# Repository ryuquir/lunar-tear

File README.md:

# Lunar Tear

Private server research project for a certain discontinued mobile game.
Discord server: https://discord.gg/G3anrfcV

## How To Launch The Server

### Prerequisites

- Go 1.24+
- Populated `server/assets/` directory

### Regenerate protobuf stubs

```bash
cd server
make proto
```

### Run

```bash
cd server
sudo go run ./cmd/lunar-tear \
  --host 10.0.2.2 \
  --http-port 8080 \
  --scene 13
```

`sudo` is needed because gRPC binds to port 443 (privileged). On Linux you can use `setcap` instead:

```bash
go build -o lunar-tear ./cmd/lunar-tear
sudo setcap cap_net_bind_service=+ep ./lunar-tear
./lunar-tear --host 10.0.2.2 --http-port 8080 --scene 13
```

### Ports

| Protocol | Port | Notes                                                |
| -------- | ---- | ---------------------------------------------------- |
| gRPC     | 443  | hardcoded by the client, not configurable            |
| HTTP     | 8080 | Octo asset API + game web pages (`--http-port` flag) |

### Flags

| Flag                   | Default             | Description                                              |
| ---------------------- | ------------------- | -------------------------------------------------------- |
| `--host`               | `127.0.0.1`         | hostname/IP given to the client                          |
| `--http-port`          | `8080`              | HTTP/Octo server port                                    |
| `--resources-base-url` | (derived from host) | base URL for list.bin rewrite (must be exactly 43 chars) |
| `--scene`              | `0`                 | bootstrap new users to scene N (0 = fresh start)         |

### `--resources-base-url`

Overrides the base URL the client uses to fetch resources. The replacement string **must be exactly 43 characters**. If omitted, the server derives it from `--host` and `--http-port` automatically (when the result happens to be 43 characters). If the length doesn't match, the server logs a warning and serves the resource list unchanged.

```bash
sudo go run ./cmd/lunar-tear \
  --host 10.0.2.2 \
  --http-port 8080 \
  --resources-base-url "http://192.168.1.50:8080/res-bundle-srv" \
  --scene 13
```

> **Tip:** verify the length with `printf "your-url-here" | wc -c`.

## ⚠️ Legal Disclaimer

**Lunar Tear** is a fan-made, non-commercial **preservation and research project** dedicated to keeping a certain discontinued mobile game playable for educational and archival purposes.

- This project is **not affiliated with**, **endorsed by**, or **approved by** the original publisher or any of its subsidiaries.
- All trademarks, copyrights, and intellectual property related to the original game and its associated franchises belong to their respective owners.
- All code in this repository is original work developed through clean-room reverse engineering for interoperability with the game client.
- No copyrighted game assets, binaries, or master data are distributed in this repository.

**Use at your own risk.** The author assumes no liability for any damages or legal consequences that may arise from using this software. By using or contributing to this project, you are solely responsible for ensuring your usage complies with all applicable laws in your jurisdiction.

This project is released under the [MIT License](LICENSE).

**If you are a rights holder with concerns regarding this project**, please contact me directly.

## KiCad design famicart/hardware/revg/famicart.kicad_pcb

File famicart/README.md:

# famicart — RP2040/RP2350 ファミコン・マルチマッパー・カートリッジ ファームウェア＋基板

ファミコン（NES）の公式・ライセンス品 2,233 タイトルで使われた 92 種のマッパーを調査し、その全種（タイトル数ベース **99.0%**（2,211 本）。残り 22 本はデータベース上の不良ダンプ）に加え、基板名の記録がない市販 FC ソフト用のマッパーも含めて計 98 種をソフトウェアで再現する 1 チップ・カートリッジのファームウェアです。フラッシュに書き込んだ ROM 画像からマッパーを自動判別し、プロファイル指定で「MMC5 のバンク機能 + VRC7 音源」のような拡張 IC の組み合わせも可能にします。

> **重要な前提**: Seeed Studio XIAO RP2040 は GPIO が 11 本しかなく、単体ではカートリッジバス（最低 26 本）を駆動できません。理由と数値は [docs/01_feasibility.md](docs/01_feasibility.md) を参照。そのため **rev C 基板では基板直付けの RP2350B（GPIO 48 本）がバスを担当し、XIAO RP2040 は拡張音源コプロセッサ**として同居します（[docs/04_hardware.md](docs/04_hardware.md) の rev C 節）。rev A/B は Pico / Pico 2 モジュール 1 個の構成です。

## 状態（フェーズ 1・2 完了、フェーズ 3 = 実機検証 待ち）

| 項目 | 状態 |
|---|---|
| マッパー調査・集計（Mesen DB 由来） | 完了 → [docs/03_mapper_coverage.md](docs/03_mapper_coverage.md) |
| コア（バンク表・マッパー 99 種〔ライセンス品の 98 種＋自作向けのマッパー 30（UNROM 512、フラッシュ自己書き込み対応）〕・ROM 判別・DB 2,840 件・プロファイル） | 実装済み、ホストテスト 2,122 チェック通過 |
| 拡張音源レジスタ・ルーター（組み合わせ機構） | 実装済み |
| 拡張音源の合成（VRC6/VRC7/MMC5/N163/5B/FDS、`src/core/audio/synth.c`） | 実装済み（6 音源とも発音をホストテストで確認、VRC7 は OPLL 近似）。rev C では XIAO 側で動作 |
| PIO バス・フロントエンド、2 コア処理、PWM 音声出力 | 実装済み・**実機未検証** |
| USB-CDC コマンド（INFO / RESET / BOOTSEL / LOAD / PROFILE）と転送ツール `tools/fcload.py` | 実装済み・**実機未検証** |
| Pico / Pico 2 / RP2350B / XIAO（コプロセッサ）向けビルド | 通過（Pico: text 120KB, BSS 249KB / RP2350B: text 106KB, BSS 512KB / XIAO audio: text 42KB） |
| 2 MCU 間 UART リンク（3 Mbaud、音源レジスタのストリーム） | 実装済み・**実機未検証** |
| 回路図・基板 rev B（Pico 2、KiCad 7、90×46.1 mm〔※外形は旧寸法で切り欠きなし＝基板単体用。[04](docs/04_hardware.md) の訂正を参照〕、USB-C・リセット付き、未接続 0・DRC 0）・ガーバー・JLCPCB 実装パッケージ | [hardware/](hardware/)、[hardware/jlcpcb/](hardware/jlcpcb/) |
| 回路図・基板 rev C（RP2350B + XIAO RP2040、USB 3 口、リセット端子 J2、未接続 0・DRC 0）・ガーバー・JLCPCB 実装パッケージ | [hardware/revc/](hardware/revc/) |
| 回路図・基板 rev D（**実機動作の本命**: 実カセット型分離構成、RP2350B×2 マッパーチップ + PRG/CHR パラレル NOR 64 MB×2 + F-RAM 128 KB + CHR SRAM 512 KB、**6 層、未接続 0・DRC エラー 0**、起動バンク付き）・ガーバー・JLCPCB 実装パッケージ | [hardware/revd/](hardware/revd/)、[hardware/revd/jlcpcb/](hardware/revd/jlcpcb/)、docs/04_hardware.md の rev D 節 |
| 回路図・基板 rev E（※外形は旧寸法で切り欠きなし＝基板単体用。標準シェルには Pico 2 が 1 枚しか入らないため rev E は標準シェル不可、[04 の訂正](docs/04_hardware.md)）（**実際に作れる安価な版**: Pico 2 ×2 + XIAO RP2350、JLCPCB Basic 部品のみ 10 種・45 点、2 層、未接続 0・DRC エラー 0、MMC5 完全対応の配線）・ガーバー・JLCPCB 実装パッケージ | [hardware/reve/](hardware/reve/)、[docs/06_rev_e_plan.md](docs/06_rev_e_plan.md) |
| 回路図・基板 **rev F2**（rev F の回路を**任天堂の大型シェル**に合わせ、4 資料から作った外形〔切り欠き・スリット・リブ回避。実物では未確認〕で配置、90 × 85.7 mm、Pico 2 ×4 + XIAO、Basic 部品のみ 10 種・54 点、2 層、**未接続 0・DRC エラー 0**） | [hardware/revf2/](hardware/revf2/)、[docs/10_rev_f_board.md](docs/10_rev_f_board.md) |
| 回路図・基板 **rev G**（Pico 2 ×2 ＋ XIAO RP2350 ×2 を基本に、増設 Pico 2 ×2〔512 KB 級の PRG・CHR 用、任意〕、16 MB フラッシュ、microSD〔任意〕。任天堂の大型シェル用 89.6 × 85.7 mm、2 層、Basic 部品のみ 10 種・81 点、**未接続 0・DRC エラー 0**。外形・ビア・シルク・端子部を JLCPCB の製造条件に合わせ、Standard PCBA 用の注文パッケージ（捨て基板を描き込んだデータと、基板だけのデータ）を付けた。検査ツールが 2 つのガーバー ZIP の中身と捨て基板の寸法をデータから測る。設計レビューで見つかった回路の問題〔書き込みストローブ、/ROMSEL、PPU /WE、31 番端子、PPU データ線の直列抵抗など〕を修正。**実機とシェルの実物では未検証、rev G 用のファームは未作成**） | [hardware/revg/](hardware/revg/)（[外形図](hardware/revg/outline.png)、[配置図](hardware/revg/placement.png)、[注文メモ](hardware/revg/jlcpcb/README.md)）、[docs/12_rev_g_plan.md](docs/12_rev_g_plan.md)、ファミコン本体の仕様と全端子は [docs/11_famicom_reference.md](docs/11_famicom_reference.md) |
| 回路図・基板 rev F（rev E + SFC 型コプロセッサ用 Pico 2 ×2、90 × 70.1 mm、Basic 部品のみ 10 種・54 点、2 層、**未接続 0・DRC エラー 0**。外形は旧寸法で切り欠きなし＝基板単体用） | [hardware/revf/](hardware/revf/)、[docs/10_rev_f_board.md](docs/10_rev_f_board.md)、コプロセッサ ABI は [docs/09_coproc_abi.md](docs/09_coproc_abi.md) |
| rev E ファームウェア（U1 CPU バス応答・書き込み取り込み・CHR-RAM 再現・起動手順・ROM ライブラリ、U2 CHR/CIRAM /CE・MMC5 PPU 処理、U3 IRQ・拡張音源、3 台リンク） | 実装済み・3 本ともビルド通過、ホストテスト通過（rev E 分 52 項目、追加マッパー 524 項目）、**実機未検証**。[docs/07_rev_e_firmware.md](docs/07_rev_e_firmware.md) |
| rev D ファームウェア（バンク線出力、2 MCU リンク、外部フラッシュ書き込み、ROM ライブラリ、ブートスタブ） | 実装済み・ビルド通過（U1 text 130 KB / U2 37 KB）、ホストテスト通過、**実機未検証** |

## ビルド

```sh
# ホスト側ユニットテスト
cd famicart/test && make

# ファームウェア（FC_BOARD = pico | pico2 | rp2350b | xiao_audio | xiao_rp2040）
cd famicart && mkdir -p build && cd build
cmake -DPICO_SDK_PATH=/path/to/pico-sdk -DFC_BOARD=pico2 ..
make -j
# -> famicart.uf2 を BOOTSEL モードのドライブへコピー

# rev C 基板は 2 つ書く: 主 MCU（J3 を挿し SW2 を押しながら SW1 を離す）と XIAO（XIAO 自身の USB-C と BOOT ボタン）
cmake -S . -B build-rp2350b   -DFC_BOARD=rp2350b   && cmake --build build-rp2350b   # -> RP2350B へ
cmake -S . -B build-xiao_audio -DFC_BOARD=xiao_audio && cmake --build build-xiao_audio # -> XIAO RP2040 へ
```

## ROM の書き込み（自動判別）

```sh
# そのまま: ヘッダ → CRC32 DB → サイズ推定 の順で自動判別
python3 tools/rom2uf2.py game.nes -o game.uf2 --family rp2350

# マッパーを強制し、VRC7 音源を追加（MMC5 の機能 + VRC7 の音）
python3 tools/rom2uf2.py game.nes -o game.uf2 --mapper 5 --audio vrc7:exclusive --audio mmc5

# レジスタ窓が衝突する組み合わせは窓を移動（VRC6 のレジスタを $C000 へ）
python3 tools/rom2uf2.py game.nes -o game.uf2 --audio vrc6@0xC000
```

## 本体に挿したまま ROM を転送（USB-C）

```sh
pip install pyserial
python3 tools/fcload.py /dev/ttyACM0 info          # 判別結果・バス統計
python3 tools/fcload.py /dev/ttyACM0 load game.nes # 転送 → カートリッジ自動再起動 → 本体のリセットを押す
python3 tools/fcload.py /dev/ttyACM0 reset         # ソフトからカートリッジをリセット
python3 tools/fcload.py /dev/ttyACM0 bootsel       # ファーム更新用 UF2 モードへ
```

ROM はフラッシュ先頭から 256KB の位置（`FC_FLASH_ROM_SLOT`）に、48 バイトのプロファイル（256 バイト境界にパディング）＋画像の形で書き込まれます。ツールを介さず `.nes` を直接その位置に焼いた場合もヘッダ/DB で判別します。起動後、USB CDC（115200）に判別結果とバス統計が 2 秒ごとに出ます。

## データベースの再生成

```sh
python3 tools/gen_romdb.py   # data/MesenNesDB.txt -> src/core/romdb_gen.h, docs/03_mapper_coverage.md
```

## ドキュメント

- [01 実現可能性](docs/01_feasibility.md) — ピン数・タイミング・メモリの数値と結論
- [02 ファームウェア構成](docs/02_architecture.md) — 高速パス、マッパー IF、音源ルーター、判別フロー、既知の制約
- [03 マッパー集計](docs/03_mapper_coverage.md) — 92 種の本数・サブマッパー・代表基板・実装状況
- [04 ハードウェア](docs/04_hardware.md) — KiCad プロジェクト、基板寸法、GPIO 割当、部品表、音声ミックス回路

## 基板の再生成（KiCad 7 + Freerouting）

```sh
cd famicart/tools/pcb
python3 gen_sch.py && python3 route_pcb.py && python3 gen_bom.py && python3 gen_jlc.py            # rev B -> hardware/
FC_DESIGN=design_revc FC_HW_DIR=../../hardware/revc python3 gen_sch.py   # rev C -> hardware/revc/（route_pcb / gen_bom / gen_jlc も同じ環境変数で）
FC_DESIGN=design_revd FC_HW_DIR=../../hardware/revd FC_LAYERS=6 FC_STUBS=1 FC_TRACK=0.1 FC_CLEAR=0.1 FC_VIA=0.5 FC_VIA_DRILL=0.2 python3 route_pcb.py   # rev D（6 層）
python3 finish_route.py ../../hardware/revd/famicart.kicad_pcb   # Freerouting が残した接続を仕上げる（その後 route_pcb.py export）
```

## ロードマップ

1. **フェーズ 3**: 基板の試作・実機検証（ロジアナでタイミング確認）、配線の手直し、VRC7 音色の実機比較による校正、USB マスストレージからの ROM 選択、セーブ（バッテリ RAM）のフラッシュ退避
2. **フェーズ 4（rev D 向けファーム）**: 実装済み（バンク出力・リンク・フラッシュ書き込み・ライブラリ・ブートスタブ）。残り: 起動メニュー（コントローラでライブラリ選択）、MMC5 $5204 状態の U2→U1 同期、$6000 PRG-ROM マッパーの F-RAM コピー対応
3. **フェーズ 5（実機ブリングアップ）**: 基板到着後 `FLASHID` → `BOOTBANK` → `libadd` NROM → MMC1 → MMC3 → MMC5 の順に確認。ロジアナで M2 ↔ バンク線・/RD ↔ CHR バンク線の遅延を測る
4. 未実装マッパー（海賊版マルチカート系）は対象外のまま

## ライセンス・出典

ファームウェアはリポジトリのライセンスに従います。`data/MesenNesDB.txt` は Mesen プロジェクト配布の生成データ（NesCartDB および NewRisingSun の NES 2.0 header database 由来）で、マッパー判別用のメタデータのみを利用しています。ゲーム ROM は含みません。

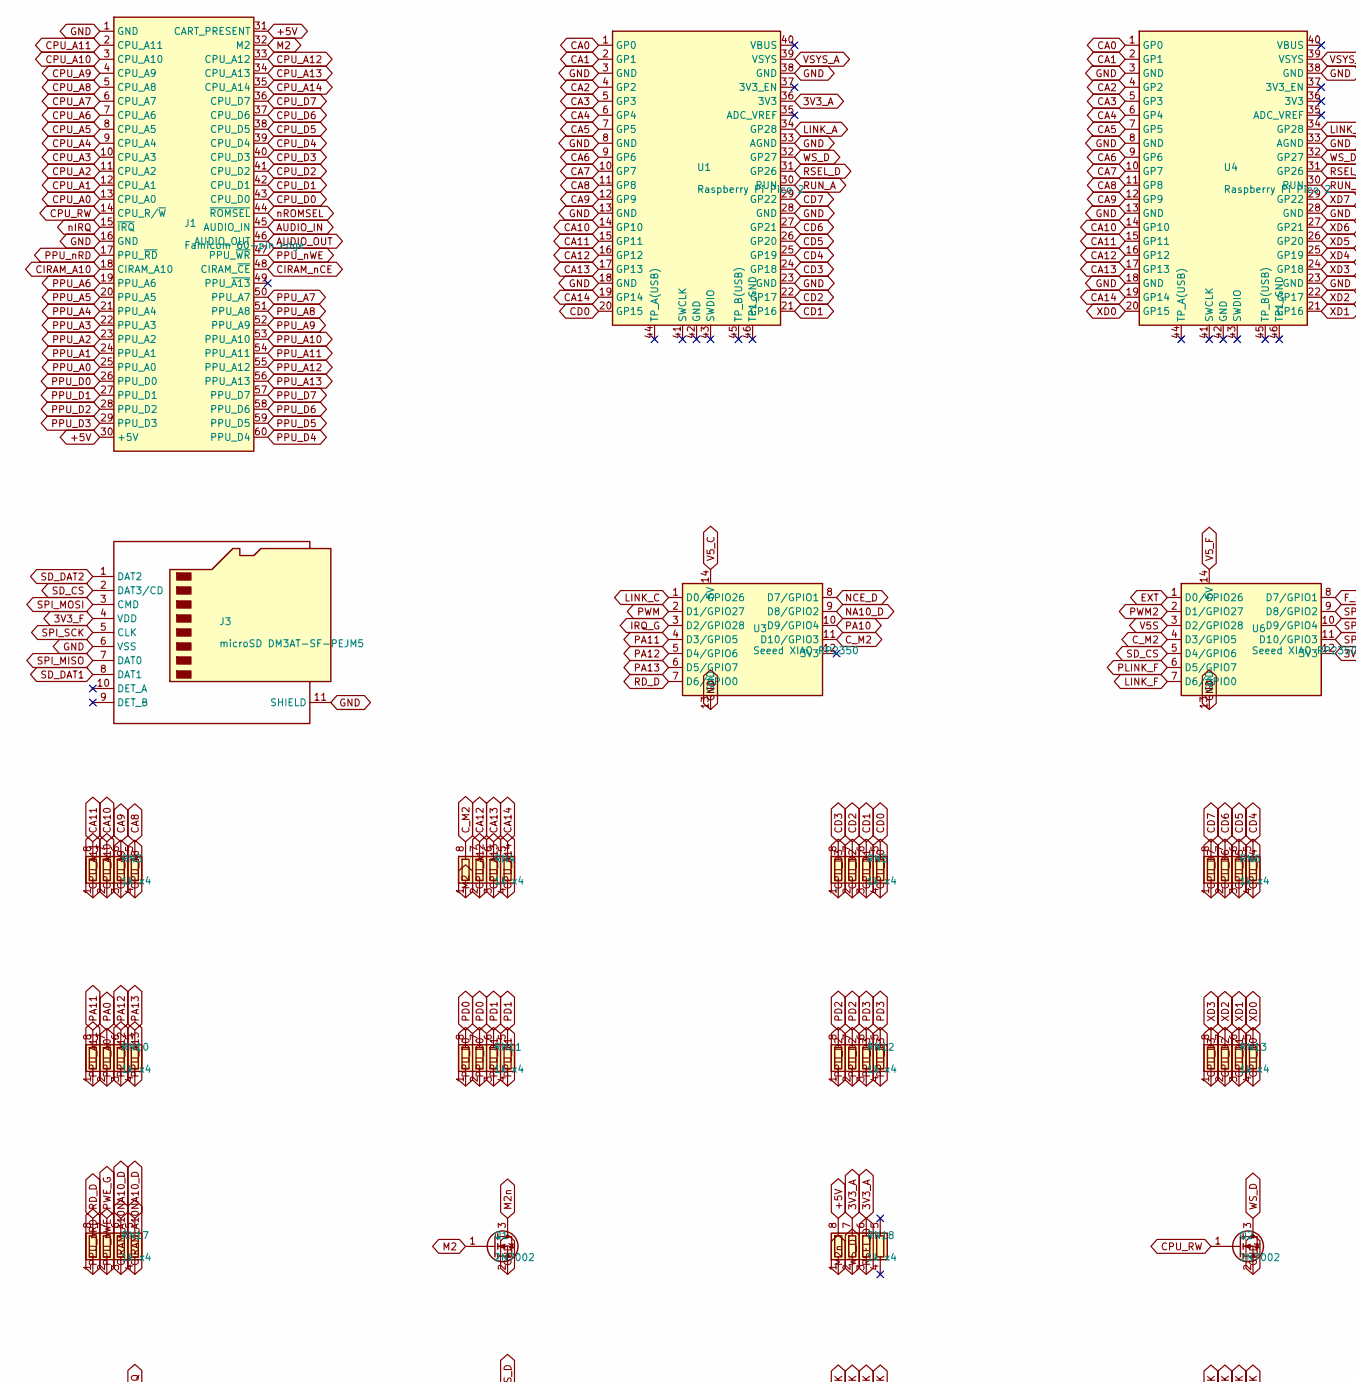
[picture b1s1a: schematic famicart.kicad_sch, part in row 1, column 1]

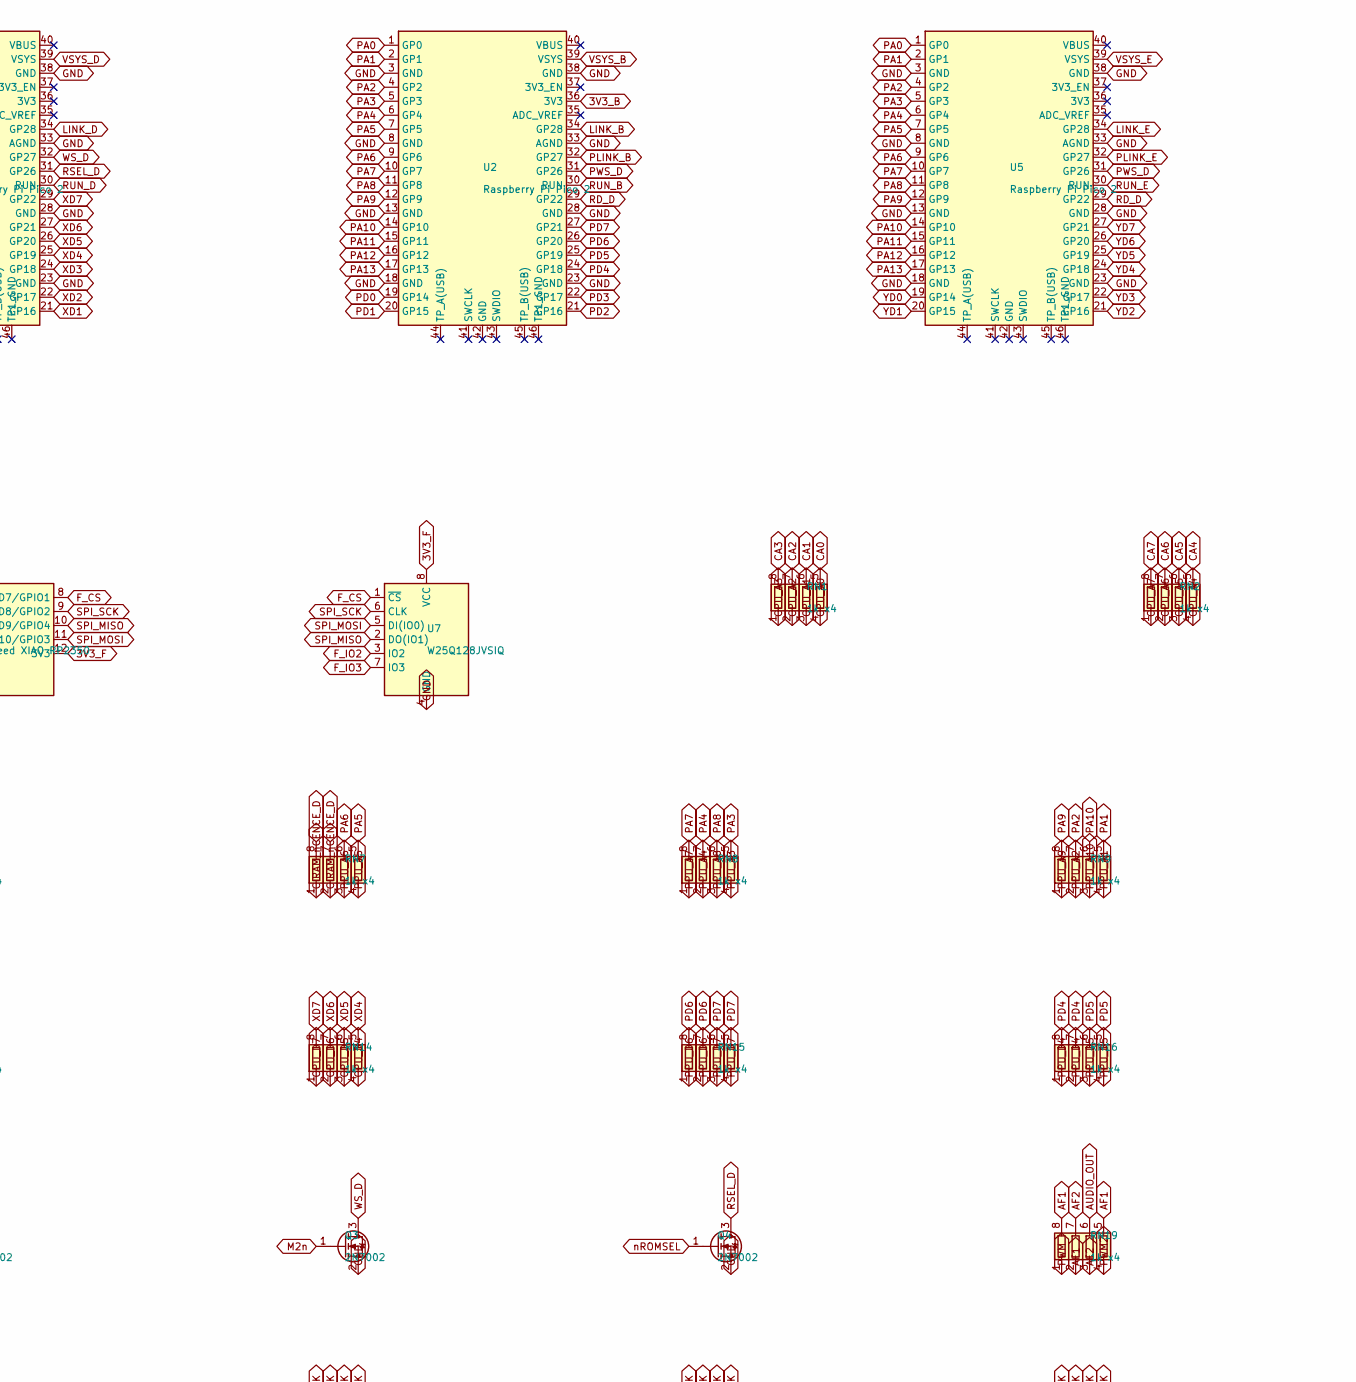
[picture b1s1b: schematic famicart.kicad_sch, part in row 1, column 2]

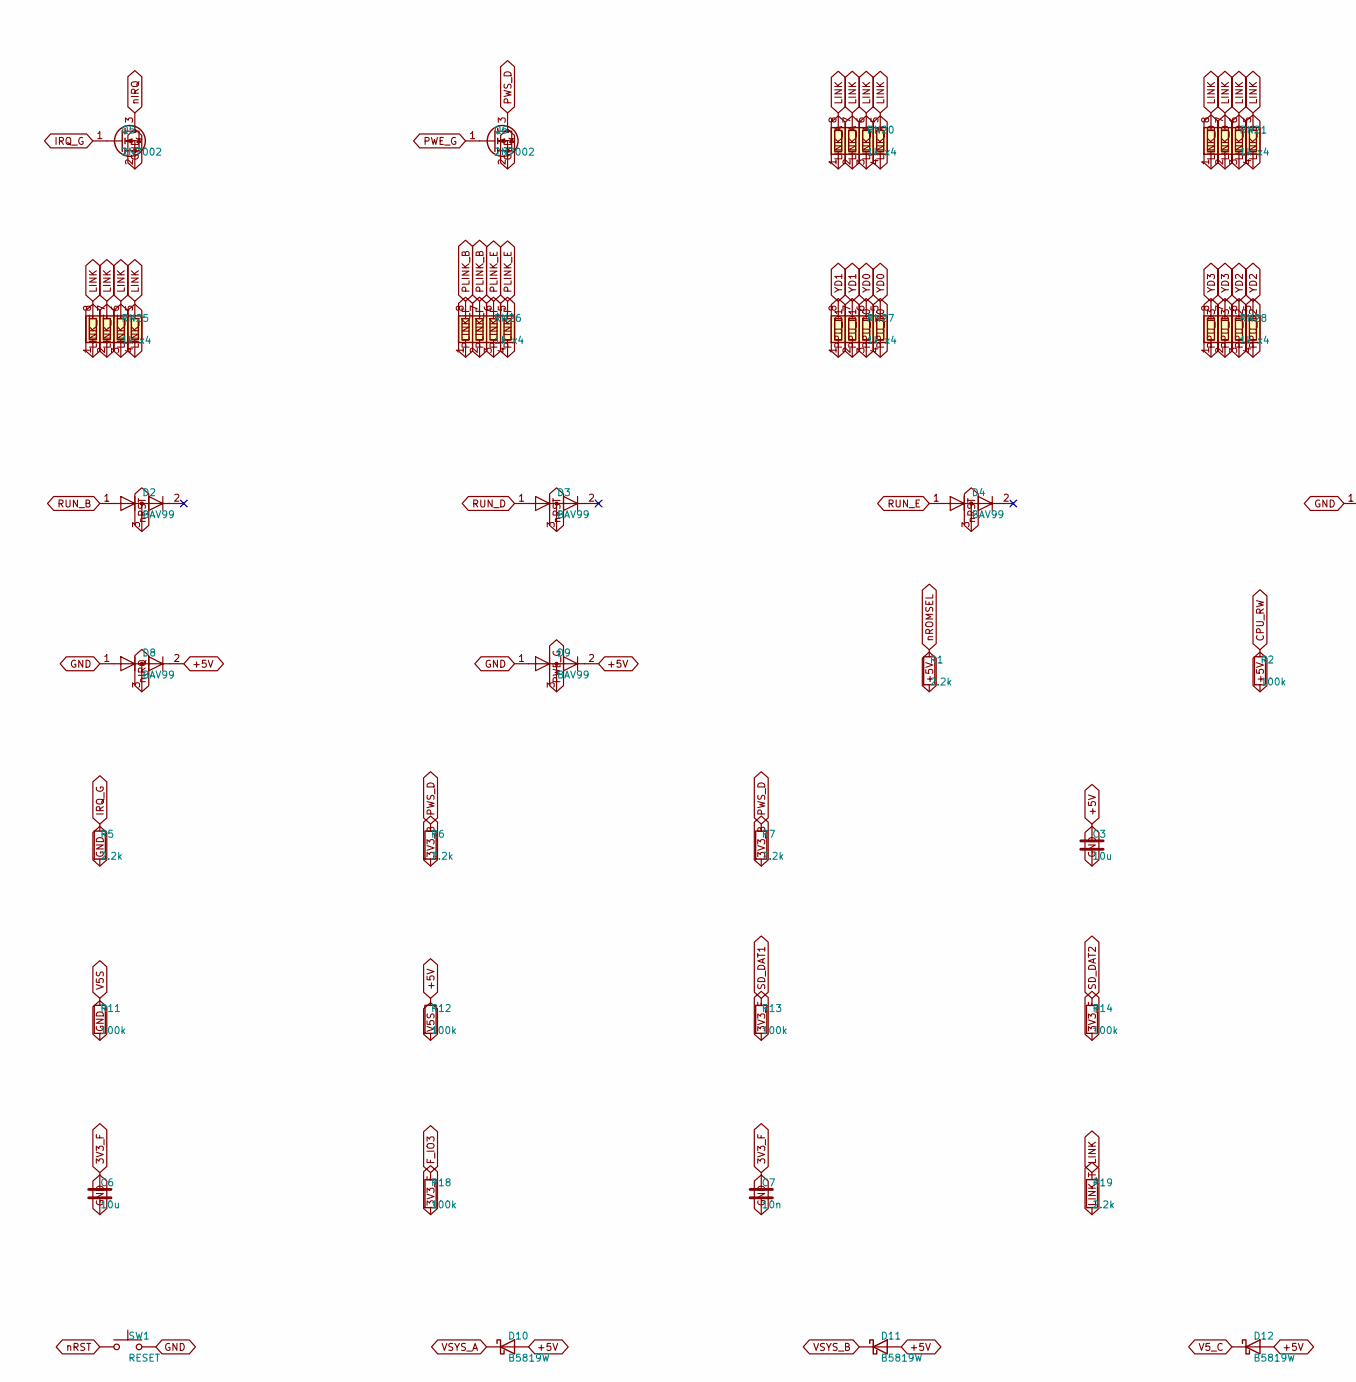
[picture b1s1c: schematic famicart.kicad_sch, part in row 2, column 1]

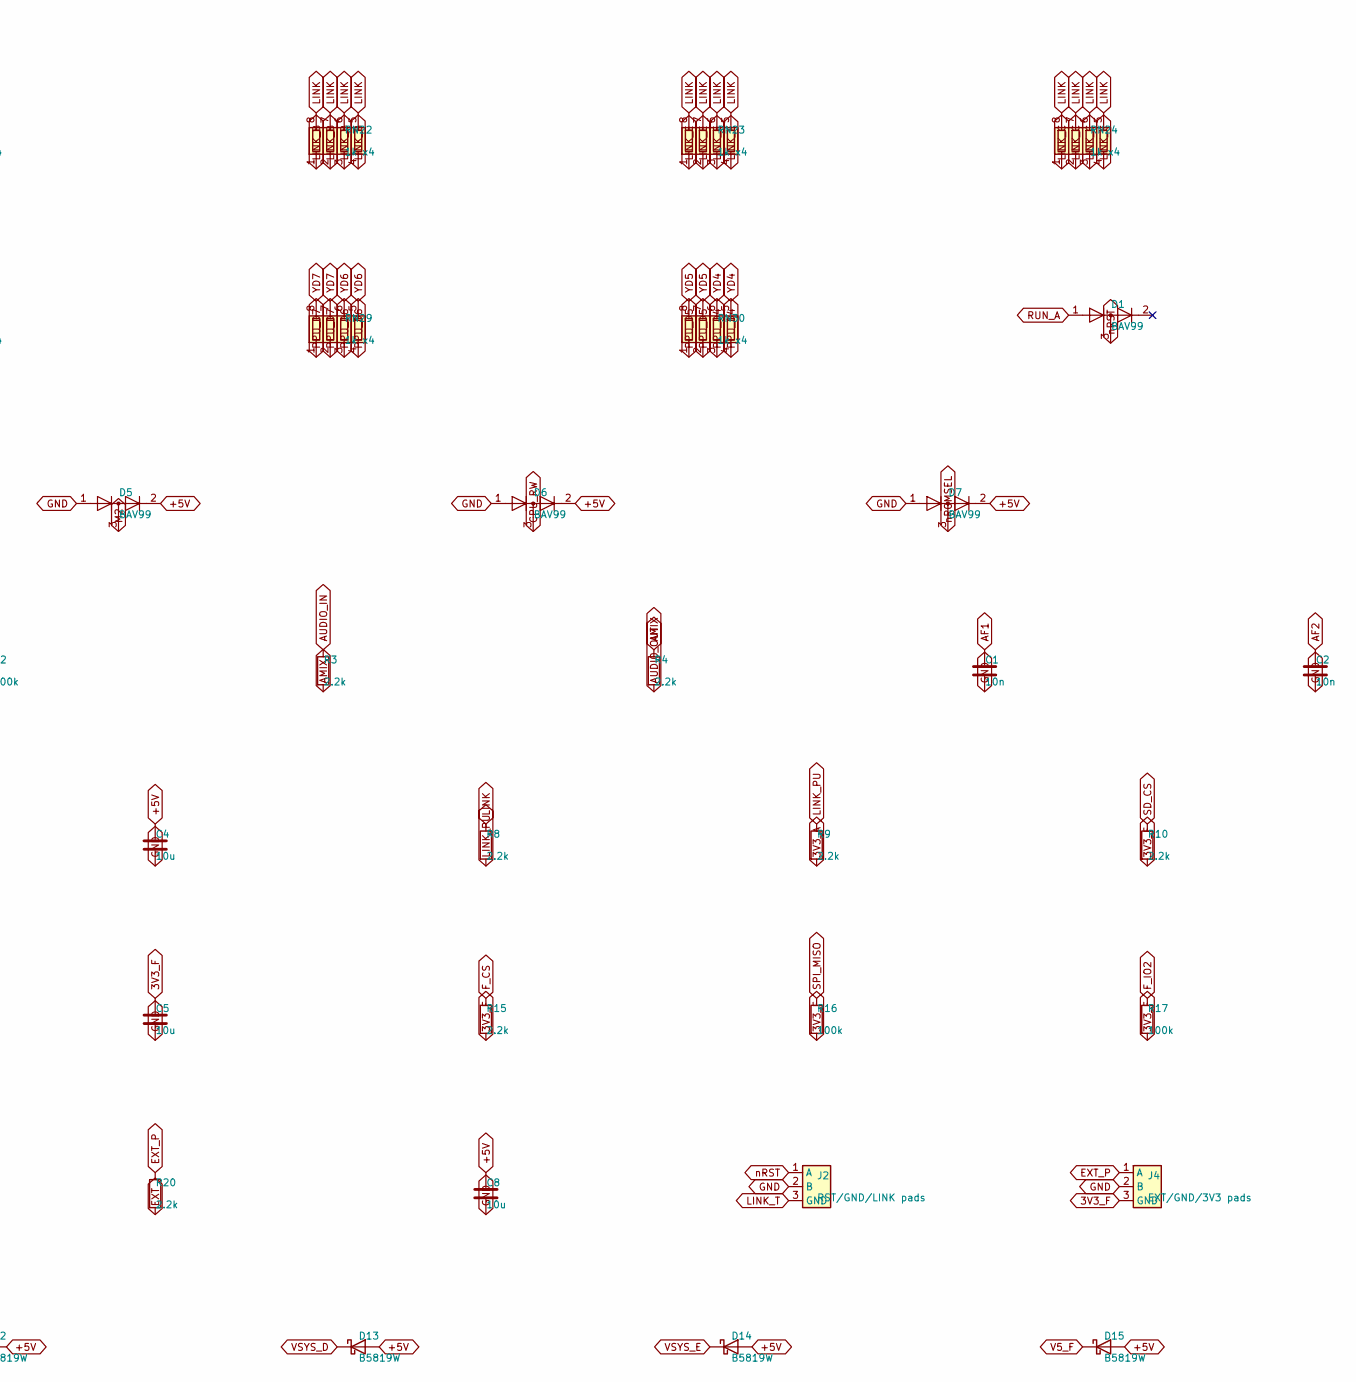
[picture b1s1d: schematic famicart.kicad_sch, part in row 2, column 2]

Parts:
C1, C2, C7: 10n; C_0603_1608Metric
C3, C4, C5, C6, C8: 10u; C_0805_2012Metric
D1, D2, D3, D4, D5, D6, D7, D8, D9: BAV99; SOT-23
D10, D11, D12, D13, D14, D15: B5819W; D_SOD-123
J1: Famicom 60-pin edge; Famicom_CardEdge_60
J2: RST/GND/LINK pads; WirePads_1x3
J3: microSD DM3AT-SF-PEJM5; microSD_HC_Hirose_DM3AT-SF-PEJM5
J4: EXT/GND/3V3 pads; WirePads_1x3
Q1, Q2, Q3, Q4, Q5, Q6: 2N7002; SOT-23
R1, R3, R4, R5, R6, R7, R8, R9, R10, R15, R19, R20: 2.2k; R_0603_1608Metric
R2, R11, R12, R13, R14, R16, R17, R18: 100k; R_0603_1608Metric
RN1, RN2, RN3, RN4, RN5, RN6, RN7, RN8, RN9, RN10, RN11, RN12, RN13, RN14, RN15, RN16, RN17, RN18, RN19, RN20, RN21, RN22, RN23, RN24, RN25, RN26, RN27, RN28, RN29, RN30: 1k x4; R_Array_Convex_4x0603
SW1: RESET; SW_Push_1P1T_XKB_TS-1187A
U1, U2, U4, U5: Raspberry Pi Pico 2; RPi_Pico_SMD_Short
U3, U6: Seeed XIAO RP2350; XIAO-RP2350-Edge
U7: W25Q128JVSIQ; SOIC-8_5.23x5.23mm_P1.27mm

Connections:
3V3_A: R9.2, RN18.6 (R3.2), RN18.7 (R2.2), U1.36 (3V3)
3V3_B: R6.2, R7.2, U2.36 (3V3)
3V3_F: C5.1, C6.1, C7.1, J3.4 (VDD), J4.3 (GND), R10.2, R13.2, R14.2, R15.2, R16.2, R17.2, R18.2, U6.12 (3V3), U7.8 (VCC)
+5V: C3.1, C4.1, C8.1, D5.2 (A), D6.2 (A), D7.2 (A), D8.2 (A), D9.2 (A), D10.2 (A), D11.2 (A), D12.2 (A), D13.2 (A), D14.2 (A), D15.2 (A), J1.30 (+5V), J1.31 (CART_PRESENT), R1.2, R2.2, R12.1, RN18.8 (R1.2)
AF1: C1.1, RN19.2 (R2.1), RN19.5 (R4.2), RN19.8 (R1.2)
AF2: C2.1, RN19.3 (R3.1), RN19.7 (R2.2)
AMIX: R3.2, R4.1
AUDIO_IN: J1.45 (AUDIO_IN), R3.1
AUDIO_OUT: J1.46 (AUDIO_OUT), R4.2, RN19.6 (R3.2)
CA0: RN1.5 (R4.2), U1.1 (GP0), U4.1 (GP0)
CA1: RN1.6 (R3.2), U1.2 (GP1), U4.2 (GP1)
CA2: RN1.7 (R2.2), U1.4 (GP2), U4.4 (GP2)
CA3: RN1.8 (R1.2), U1.5 (GP3), U4.5 (GP3)
CA4: RN2.5 (R4.2), U1.6 (GP4), U4.6 (GP4)
CA5: RN2.6 (R3.2), U1.7 (GP5), U4.7 (GP5)
CA6: RN2.7 (R2.2), U1.9 (GP6), U4.9 (GP6)
CA7: RN2.8 (R1.2), U1.10 (GP7), U4.10 (GP7)
CA8: RN3.5 (R4.2), U1.11 (GP8), U4.11 (GP8)
CA9: RN3.6 (R3.2), U1.12 (GP9), U4.12 (GP9)
CA10: RN3.7 (R2.2), U1.14 (GP10), U4.14 (GP10)
CA11: RN3.8 (R1.2), U1.15 (GP11), U4.15 (GP11)
CA12: RN4.7 (R2.2), U1.16 (GP12), U4.16 (GP12)
CA13: RN4.6 (R3.2), U1.17 (GP13), U4.17 (GP13)
CA14: RN4.5 (R4.2), U1.19 (GP14), U4.19 (GP14)
CD0: RN5.5 (R4.2), U1.20 (GP15)
CD1: RN5.6 (R3.2), U1.21 (GP16)
CD2: RN5.7 (R2.2), U1.22 (GP17)
CD3: RN5.8 (R1.2), U1.24 (GP18)
CD4: RN6.5 (R4.2), U1.25 (GP19)
CD5: RN6.6 (R3.2), U1.26 (GP20)
CD6: RN6.7 (R2.2), U1.27 (GP21)
CD7: RN6.8 (R1.2), U1.29 (GP22)
CIRAM_A10: J1.18 (CIRAM_A10), RN17.3 (R3.1), RN17.4 (R4.1)
CIRAM_nCE: J1.48 (CIRAM_~CE), RN7.1 (R1.1), RN7.2 (R2.1)
CPU_A0: J1.13 (CPU_A0), RN1.4 (R4.1)
CPU_A1: J1.12 (CPU_A1), RN1.3 (R3.1)
CPU_A2: J1.11 (CPU_A2), RN1.2 (R2.1)
CPU_A3: J1.10 (CPU_A3), RN1.1 (R1.1)
CPU_A4: J1.9 (CPU_A4), RN2.4 (R4.1)
CPU_A5: J1.8 (CPU_A5), RN2.3 (R3.1)
CPU_A6: J1.7 (CPU_A6), RN2.2 (R2.1)
CPU_A7: J1.6 (CPU_A7), RN2.1 (R1.1)
CPU_A8: J1.5 (CPU_A8), RN3.4 (R4.1)
CPU_A9: J1.4 (CPU_A9), RN3.3 (R3.1)
CPU_A10: J1.3 (CPU_A10), RN3.2 (R2.1)
CPU_A11: J1.2 (CPU_A11), RN3.1 (R1.1)
CPU_A12: J1.33 (CPU_A12), RN4.2 (R2.1)
CPU_A13: J1.34 (CPU_A13), RN4.3 (R3.1)
CPU_A14: J1.35 (CPU_A14), RN4.4 (R4.1)
CPU_D0: J1.43 (CPU_D0), RN5.4 (R4.1), RN13.4 (R4.1)
CPU_D1: J1.42 (CPU_D1), RN5.3 (R3.1), RN13.3 (R3.1)
CPU_D2: J1.41 (CPU_D2), RN5.2 (R2.1), RN13.2 (R2.1)
CPU_D3: J1.40 (CPU_D3), RN5.1 (R1.1), RN13.1 (R1.1)
CPU_D4: J1.39 (CPU_D4), RN6.4 (R4.1), RN14.4 (R4.1)
CPU_D5: J1.38 (CPU_D5), RN6.3 (R3.1), RN14.3 (R3.1)
CPU_D6: J1.37 (CPU_D6), RN6.2 (R2.1), RN14.2 (R2.1)
CPU_D7: J1.36 (CPU_D7), RN6.1 (R1.1), RN14.1 (R1.1)
CPU_RW: D6.3 (K), J1.14 (CPU_R/~W), Q2.1 (G), R2.1
C_M2: RN4.8 (R1.2), U3.11 (D10/GPIO3), U6.4 (D3/GPIO5)
EXT: R20.2, U6.1 (D0/GPIO26)
EXT_P: J4.1 (A), R20.1
F_CS: R15.1, U6.8 (D7/GPIO1), U7.1 (~CS)
F_IO2: R17.1, U7.3 (IO2)
F_IO3: R18.1, U7.7 (IO3)
GND: C1.2, C2.2, C3.2, C4.2, C5.2, C6.2, C7.2, C8.2, D5.1 (K), D6.1 (K), D7.1 (K), D8.1 (K), D9.1 (K), J1.1 (GND), J1.16 (GND), J2.2 (B), J3.6 (VSS), J3.11 (SHIELD), J4.2 (B), Q1.2 (S), Q2.2 (S), Q3.2 (S), Q4.2 (S), Q5.2 (S), Q6.2 (S), R5.2, R11.2, SW1.2, U1.3 (GND), U1.8 (GND), U1.13 (GND), U1.18 (GND), U1.23 (GND), U1.28 (GND), U1.33 (AGND), U1.38 (GND), U2.3 (GND), U2.8 (GND), U2.13 (GND), U2.18 (GND), U2.23 (GND), U2.28 (GND), U2.33 (AGND), U2.38 (GND), U3.13 (GND), U4.3 (GND), U4.8 (GND), U4.13 (GND), U4.18 (GND), U4.23 (GND), U4.28 (GND), U4.33 (AGND), U4.38 (GND), U5.3 (GND), U5.8 (GND), U5.13 (GND), U5.18 (GND), U5.23 (GND), U5.28 (GND), U5.33 (AGND), U5.38 (GND), U6.13 (GND), U7.4 (GND)
IRQ_G: Q5.1 (G), R5.1, U3.3 (D2/GPIO28)
LINK: R8.1, R19.1, RN20.5 (R4.2), RN20.6 (R3.2), RN20.7 (R2.2), RN20.8 (R1.2), RN21.5 (R4.2), RN21.6 (R3.2), RN21.7 (R2.2), RN21.8 (R1.2), RN22.5 (R4.2), RN22.6 (R3.2), RN22.7 (R2.2), RN22.8 (R1.2), RN23.5 (R4.2), RN23.6 (R3.2), RN23.7 (R2.2), RN23.8 (R1.2), RN24.5 (R4.2), RN24.6 (R3.2), RN24.7 (R2.2), RN24.8 (R1.2), RN25.5 (R4.2), RN25.6 (R3.2), RN25.7 (R2.2), RN25.8 (R1.2)
LINK_A: RN20.1 (R1.1), RN20.2 (R2.1), RN20.3 (R3.1), RN20.4 (R4.1), U1.34 (GP28)
LINK_B: RN22.1 (R1.1), RN22.2 (R2.1), RN22.3 (R3.1), RN22.4 (R4.1), U2.34 (GP28)
LINK_C: RN24.1 (R1.1), RN24.2 (R2.1), RN24.3 (R3.1), RN24.4 (R4.1), U3.1 (D0/GPIO26)
LINK_D: RN21.1 (R1.1), RN21.2 (R2.1), RN21.3 (R3.1), RN21.4 (R4.1), U4.34 (GP28)
LINK_E: RN23.1 (R1.1), RN23.2 (R2.1), RN23.3 (R3.1), RN23.4 (R4.1), U5.34 (GP28)
LINK_F: RN25.1 (R1.1), RN25.2 (R2.1), RN25.3 (R3.1), RN25.4 (R4.1), U6.7 (D6/GPIO0)
LINK_PU: R8.2, R9.1
LINK_T: J2.3 (GND), R19.2
M2: D5.3 (K), J1.32 (M2), Q1.1 (G), RN4.1 (R1.1)
M2n: Q1.3 (D), Q3.1 (G), RN18.1 (R1.1)
NA10_D: RN17.5 (R4.2), RN17.6 (R3.2), U3.9 (D8/GPIO2)
NCE_D: RN7.7 (R2.2), RN7.8 (R1.2), U3.8 (D7/GPIO1)
PA0: RN10.7 (R2.2), U2.1 (GP0), U5.1 (GP0)
PA1: RN9.5 (R4.2), U2.2 (GP1), U5.2 (GP1)
PA2: RN9.7 (R2.2), U2.4 (GP2), U5.4 (GP2)
PA3: RN8.5 (R4.2), U2.5 (GP3), U5.5 (GP3)
PA4: RN8.7 (R2.2), U2.6 (GP4), U5.6 (GP4)
PA5: RN7.5 (R4.2), U2.7 (GP5), U5.7 (GP5)
PA6: RN7.6 (R3.2), U2.9 (GP6), U5.9 (GP6)
PA7: RN8.8 (R1.2), U2.10 (GP7), U5.10 (GP7)
PA8: RN8.6 (R3.2), U2.11 (GP8), U5.11 (GP8)
PA9: RN9.8 (R1.2), U2.12 (GP9), U5.12 (GP9)
PA10: RN9.6 (R3.2), U2.14 (GP10), U3.10 (D9/GPIO4), U5.14 (GP10)
PA11: RN10.8 (R1.2), U2.15 (GP11), U3.4 (D3/GPIO5), U5.15 (GP11)
PA12: RN10.6 (R3.2), U2.16 (GP12), U3.5 (D4/GPIO6), U5.16 (GP12)
PA13: RN10.5 (R4.2), U2.17 (GP13), U3.6 (D5/GPIO7), U5.17 (GP13)
PD0: RN11.7 (R2.2), RN11.8 (R1.2), U2.19 (GP14)
PD1: RN11.5 (R4.2), RN11.6 (R3.2), U2.20 (GP15)
PD2: RN12.7 (R2.2), RN12.8 (R1.2), U2.21 (GP16)
PD3: RN12.5 (R4.2), RN12.6 (R3.2), U2.22 (GP17)
PD4: RN16.7 (R2.2), RN16.8 (R1.2), U2.24 (GP18)
PD5: RN16.5 (R4.2), RN16.6 (R3.2), U2.25 (GP19)
PD6: RN15.7 (R2.2), RN15.8 (R1.2), U2.26 (GP20)
PD7: RN15.5 (R4.2), RN15.6 (R3.2), U2.27 (GP21)
PLINK_B: RN26.7 (R2.2), RN26.8 (R1.2), U2.32 (GP27)
PLINK_E: RN26.5 (R4.2), RN26.6 (R3.2), U5.32 (GP27)
PLINK_F: RN26.1 (R1.1), RN26.2 (R2.1), RN26.3 (R3.1), RN26.4 (R4.1), U6.6 (D5/GPIO7)
PPU_A0: J1.25 (PPU_A0), RN10.2 (R2.1)
PPU_A1: J1.24 (PPU_A1), RN9.4 (R4.1)
PPU_A2: J1.23 (PPU_A2), RN9.2 (R2.1)
PPU_A3: J1.22 (PPU_A3), RN8.4 (R4.1)
PPU_A4: J1.21 (PPU_A4), RN8.2 (R2.1)
PPU_A5: J1.20 (PPU_A5), RN7.4 (R4.1)
PPU_A6: J1.19 (PPU_A6), RN7.3 (R3.1)
PPU_A7: J1.50 (PPU_A7), RN8.1 (R1.1)
PPU_A8: J1.51 (PPU_A8), RN8.3 (R3.1)
PPU_A9: J1.52 (PPU_A9), RN9.1 (R1.1)
PPU_A10: J1.53 (PPU_A10), RN9.3 (R3.1)
PPU_A11: J1.54 (PPU_A11), RN10.1 (R1.1)
PPU_A12: J1.55 (PPU_A12), RN10.3 (R3.1)
PPU_A13: J1.56 (PPU_A13), RN10.4 (R4.1)
PPU_D0: J1.26 (PPU_D0), RN11.1 (R1.1), RN11.2 (R2.1), RN27.3 (R3.1), RN27.4 (R4.1)
PPU_D1: J1.27 (PPU_D1), RN11.3 (R3.1), RN11.4 (R4.1), RN27.1 (R1.1), RN27.2 (R2.1)
PPU_D2: J1.28 (PPU_D2), RN12.1 (R1.1), RN12.2 (R2.1), RN28.3 (R3.1), RN28.4 (R4.1)
PPU_D3: J1.29 (PPU_D3), RN12.3 (R3.1), RN12.4 (R4.1), RN28.1 (R1.1), RN28.2 (R2.1)
PPU_D4: J1.60 (PPU_D4), RN16.1 (R1.1), RN16.2 (R2.1), RN30.3 (R3.1), RN30.4 (R4.1)
PPU_D5: J1.59 (PPU_D5), RN16.3 (R3.1), RN16.4 (R4.1), RN30.1 (R1.1), RN30.2 (R2.1)
PPU_D6: J1.58 (PPU_D6), RN15.1 (R1.1), RN15.2 (R2.1), RN29.3 (R3.1), RN29.4 (R4.1)
PPU_D7: J1.57 (PPU_D7), RN15.3 (R3.1), RN15.4 (R4.1), RN29.1 (R1.1), RN29.2 (R2.1)
PPU_nRD: J1.17 (PPU_~RD), RN17.1 (R1.1)
PPU_nWE: J1.47 (PPU_~WR), RN17.2 (R2.1)
PWE_G: D9.3 (K), Q6.1 (G), RN17.7 (R2.2)
PWM: RN19.1 (R1.1), U3.2 (D1/GPIO27)
PWM2: RN19.4 (R4.1), U6.2 (D1/GPIO27)
PWS_D: Q6.3 (D), R6.1, R7.1, U2.31 (GP26), U5.31 (GP26)
RD_D: RN17.8 (R1.2), U2.29 (GP22), U3.7 (D6/GPIO0), U5.29 (GP22)
RSEL_D: Q4.3 (D), RN18.3 (R3.1), U1.31 (GP26), U4.31 (GP26)
RUN_A: D1.1 (K), U1.30 (RUN)
RUN_B: D2.1 (K), U2.30 (RUN)
RUN_D: D3.1 (K), U4.30 (RUN)
RUN_E: D4.1 (K), U5.30 (RUN)
SD_CS: J3.2 (DAT3/CD), R10.1, U6.5 (D4/GPIO6)
SD_DAT1: J3.8 (DAT1), R13.1
SD_DAT2: J3.1 (DAT2), R14.1
SPI_MISO: J3.7 (DAT0), R16.1, U6.10 (D9/GPIO4), U7.2 (DO(IO1))
SPI_MOSI: J3.3 (CMD), U6.11 (D10/GPIO3), U7.5 (DI(IO0))
SPI_SCK: J3.5 (CLK), U6.9 (D8/GPIO2), U7.6 (CLK)
V5S: R11.1, R12.2, U6.3 (D2/GPIO28)
V5_C: D12.1 (K), U3.14 (5V)
V5_F: D15.1 (K), U6.14 (5V)
VSYS_A: D10.1 (K), U1.39 (VSYS)
VSYS_B: D11.1 (K), U2.39 (VSYS)
VSYS_D: D13.1 (K), U4.39 (VSYS)
VSYS_E: D14.1 (K), U5.39 (VSYS)
WS_D: Q2.3 (D), Q3.3 (D), RN18.2 (R2.1), U1.32 (GP27), U4.32 (GP27)
XD0: RN13.5 (R4.2), U4.20 (GP15)
XD1: RN13.6 (R3.2), U4.21 (GP16)
XD2: RN13.7 (R2.2), U4.22 (GP17)
XD3: RN13.8 (R1.2), U4.24 (GP18)
XD4: RN14.5 (R4.2), U4.25 (GP19)
XD5: RN14.6 (R3.2), U4.26 (GP20)
XD6: RN14.7 (R2.2), U4.27 (GP21)
XD7: RN14.8 (R1.2), U4.29 (GP22)
YD0: RN27.5 (R4.2), RN27.6 (R3.2), U5.19 (GP14)
YD1: RN27.7 (R2.2), RN27.8 (R1.2), U5.20 (GP15)
YD2: RN28.5 (R4.2), RN28.6 (R3.2), U5.21 (GP16)
YD3: RN28.7 (R2.2), RN28.8 (R1.2), U5.22 (GP17)
YD4: RN30.5 (R4.2), RN30.6 (R3.2), U5.24 (GP18)
YD5: RN30.7 (R2.2), RN30.8 (R1.2), U5.25 (GP19)
YD6: RN29.5 (R4.2), RN29.6 (R3.2), U5.26 (GP20)
YD7: RN29.7 (R2.2), RN29.8 (R1.2), U5.27 (GP21)
nIRQ: D8.3 (K), J1.15 (~IRQ), Q5.3 (D)
nROMSEL: D7.3 (K), J1.44 (~ROMSEL), Q4.1 (G), R1.1
nRST: D1.3 (K), D2.3 (K), D3.3 (K), D4.3 (K), J2.1 (A), SW1.1

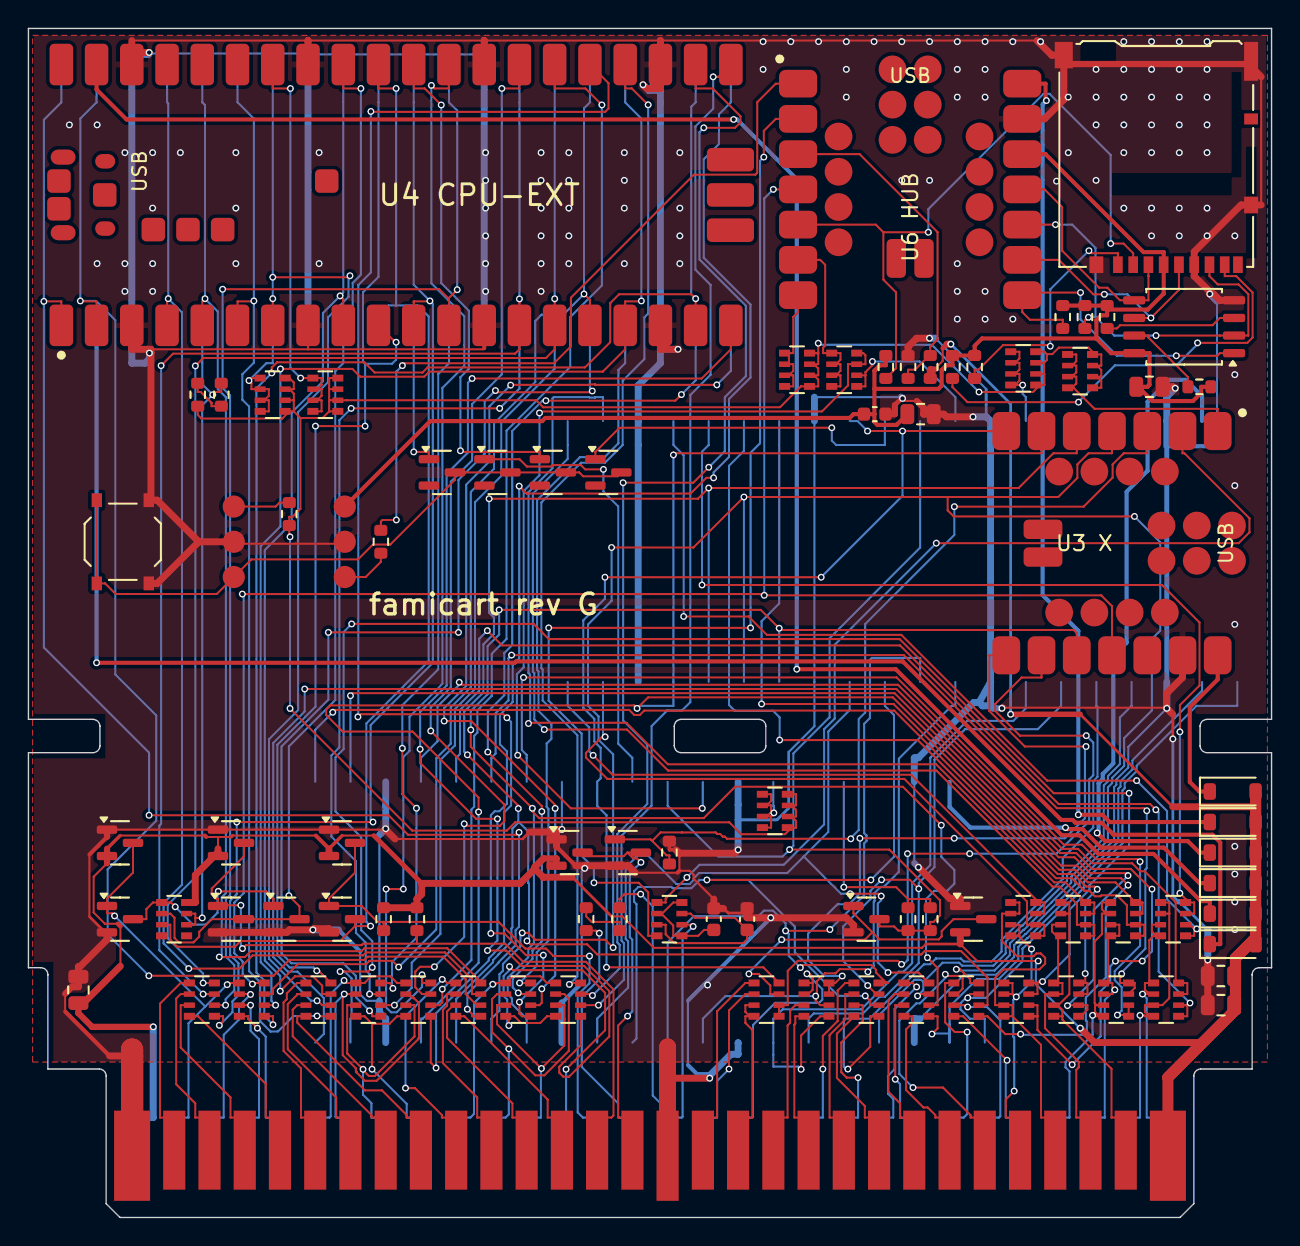
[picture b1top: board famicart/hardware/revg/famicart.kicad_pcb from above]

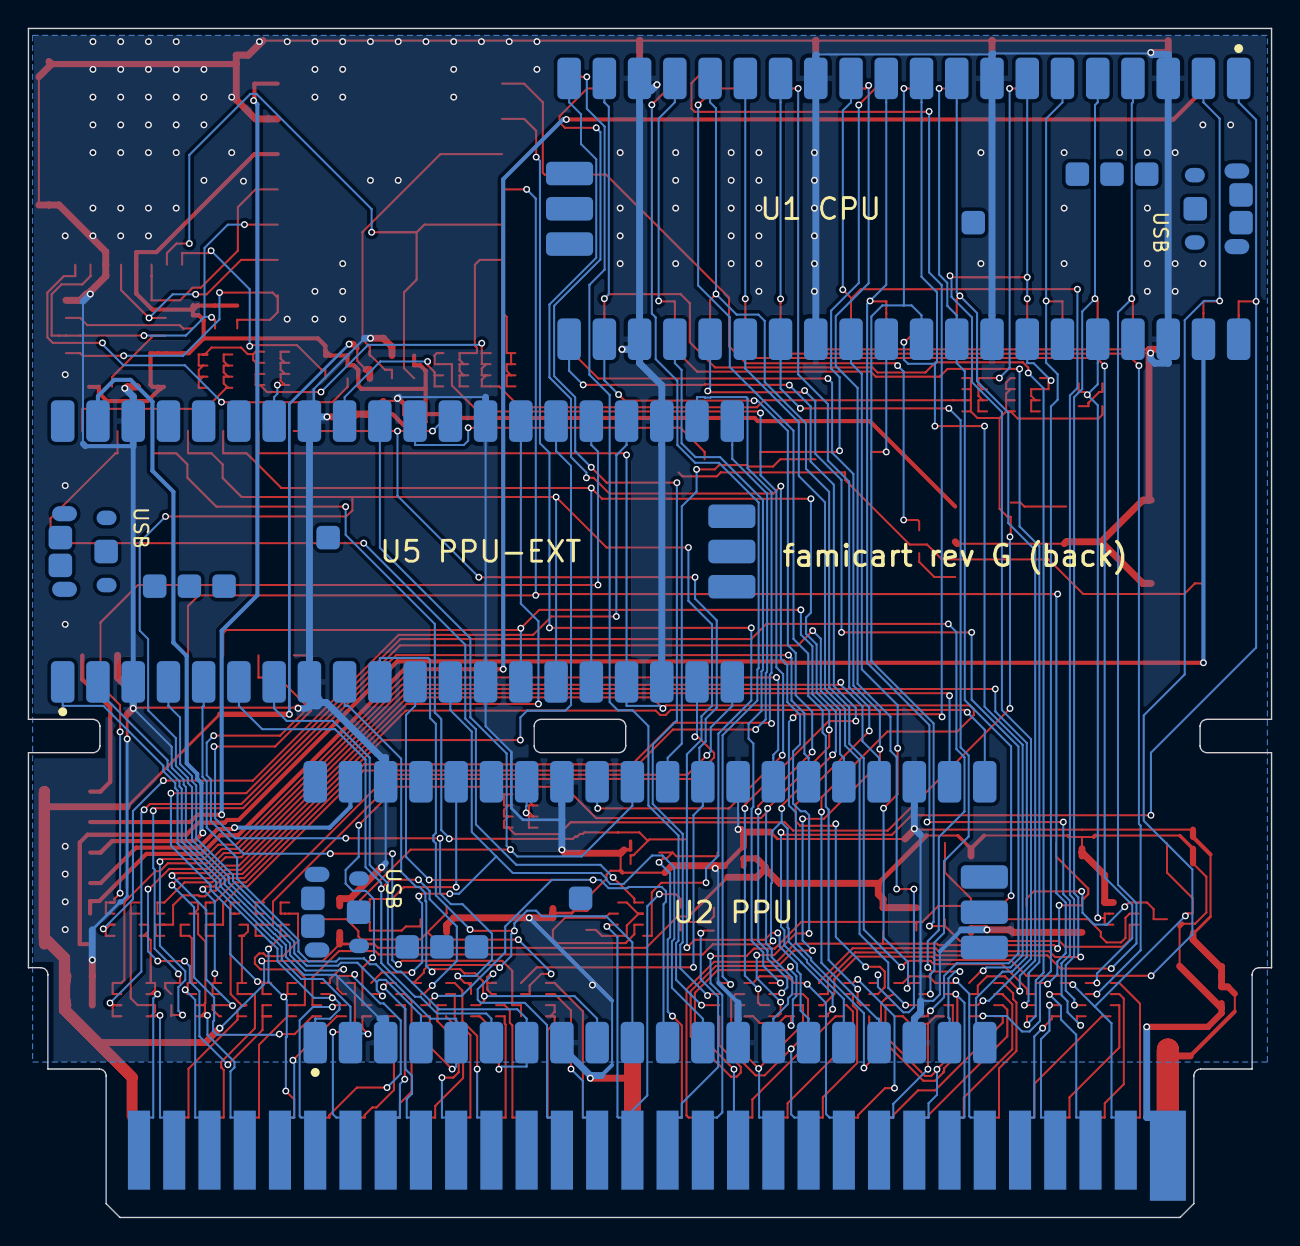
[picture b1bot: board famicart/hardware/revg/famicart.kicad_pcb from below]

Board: 2 copper layers, 89.6 x 85.7 mm, 91 parts (3 on the bottom side), 171 nets.

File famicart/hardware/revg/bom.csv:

Qty,Value,Footprint,References,Suggested part
1,Famicom 60-pin edge,Famicom_CardEdge_60,J1,"PCB card edge (gold fingers), no part"
4,Raspberry Pi Pico 2,RPi_Pico_SMD_Short,U1 U2 U4 U5,"hand-soldered: Akizuki 129604, 990 yen"
2,Seeed XIAO RP2350,XIAO-RP2350-Edge,U3 U6,"hand-soldered: Akizuki 129619, 1,100 yen"
30,1k x4,R_Array_Convex_4x0603,RN1 RN2 RN3 RN4 RN5 RN6 RN7 RN8 RN9 RN10 RN11 RN12 RN13 RN14 RN15 RN16 RN17 RN18 RN19 RN20 RN21 RN22 RN23 RN24 RN25 RN26 RN27 RN28 RN29 RN30,"4D03WGJ0102T5E 1k x4 0603 (LCSC C20197, JLCPCB Basic)"
6,2N7002,SOT-23,Q1 Q2 Q3 Q4 Q5 Q6,"2N7002 SOT-23 (LCSC C8545, JLCPCB Basic)"
12,2.2k,R_0603_1608Metric,R1 R3 R4 R5 R6 R7 R8 R9 R10 R15 R19 R20,"0603WAF2201T5E 2.2k 0603 (LCSC C4190, JLCPCB Basic)"
8,100k,R_0603_1608Metric,R2 R11 R12 R13 R14 R16 R17 R18,"0603WAF1003T5E 100k 0603 (LCSC C25803, JLCPCB Basic)"
9,BAV99,SOT-23,D1 D2 D3 D4 D5 D6 D7 D8 D9,"BAV99,215 SOT-23 (LCSC C2500, JLCPCB Basic)"
3,10n,C_0603_1608Metric,C1 C2 C7,"0603B103K500NT 10nF 0603 (LCSC C57112, JLCPCB Basic)"
6,B5819W,D_SOD-123,D10 D11 D12 D13 D14 D15,"B5819W SOD-123 (LCSC C8598, JLCPCB Basic)"
5,10u,C_0805_2012Metric,C3 C4 C5 C6 C8,"CL21A106KAYNNNE 10uF 0805 (LCSC C15850, JLCPCB Basic)"
1,W25Q128JVSIQ,SOIC-8_5.23x5.23mm_P1.27mm,U7,"W25Q128JVSIQ 16MB SPI flash SOIC-8 208mil (LCSC C97521, JLCPCB Basic)"
1,microSD DM3AT-SF-PEJM5,microSD_HC_Hirose_DM3AT-SF-PEJM5,J3,"hand-soldered: Akizuki 102395, 150 yen, optional"
1,RESET,SW_Push_1P1T_XKB_TS-1187A,SW1,"TS-1187A-B-A-B (LCSC C318884, JLCPCB Basic)"
1,RST/GND/LINK pads,WirePads_1x3,J2,
1,EXT/GND/3V3 pads,WirePads_1x3,J4,
